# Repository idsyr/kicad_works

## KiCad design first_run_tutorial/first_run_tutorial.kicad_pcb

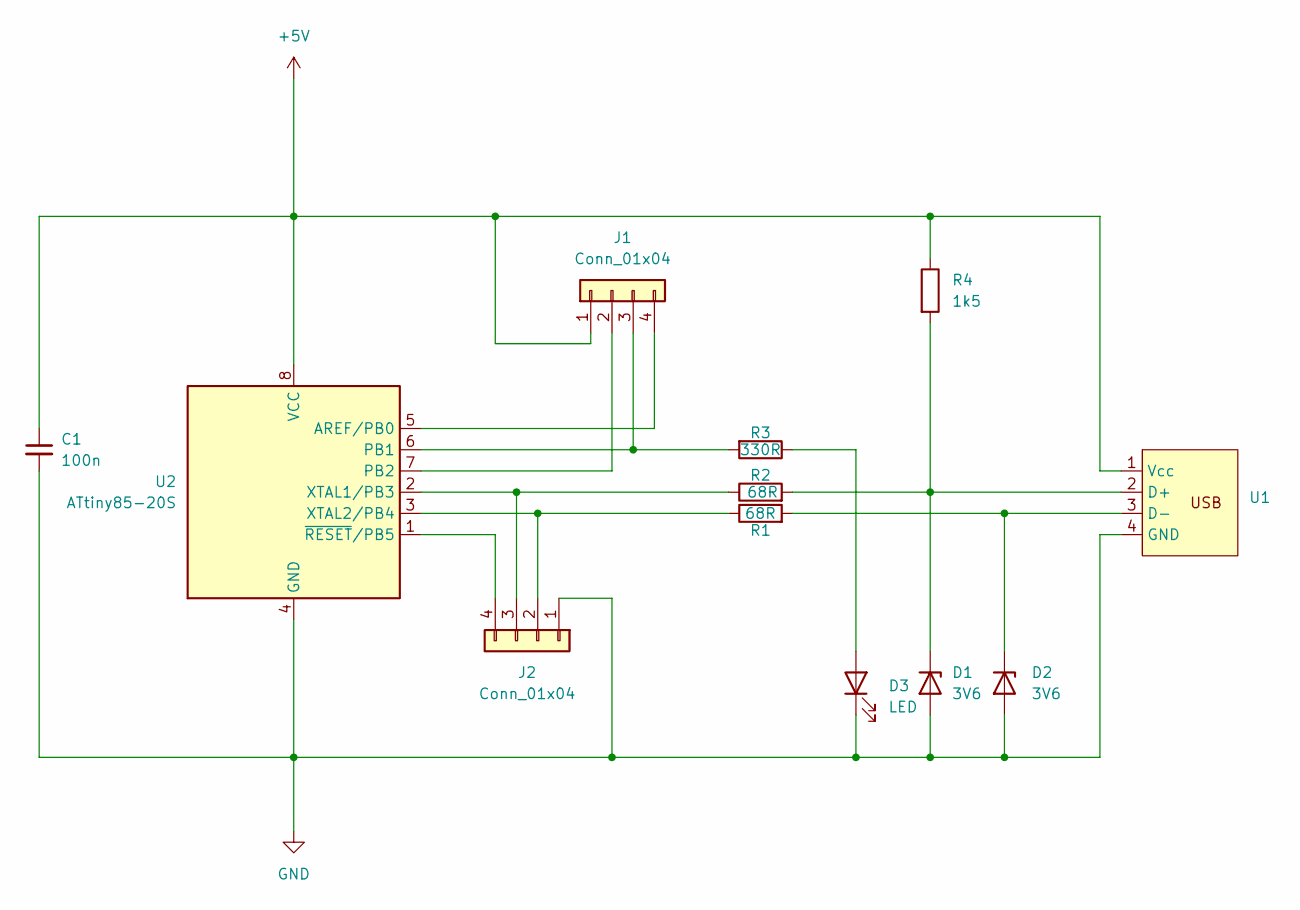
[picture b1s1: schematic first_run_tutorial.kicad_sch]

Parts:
C1: 100n; C_1206_3216Metric_Pad1.33x1.80mm_HandSolder
D1, D2: 3V6; D_SOD-123
D3: LED; LED_D3.0mm
J1, J2: Conn_01x04; PinHeader_1x04_P2.54mm_Vertical
R1, R2: 68R; R_0805_2012Metric_Pad1.20x1.40mm_HandSolder
R3: 330R; R_0805_2012Metric_Pad1.20x1.40mm_HandSolder
R4: 1k5; R_0805_2012Metric_Pad1.20x1.40mm_HandSolder
U1: PSB_USB_connector
U2: ATtiny85-20S; SOIC-8_5.3x5.3mm_P1.27mm

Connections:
+5V: C1.1, J1.1, R4.1, U1.1 (Vcc), U2.8 (VCC); also elsewhere on the board
GND: C1.2, D1.2 (A), D2.2 (A), D3.1 (K), J2.1, U1.4 (GND), U2.4 (GND); also elsewhere on the board
unnamed 2: D1.1 (K), R2.2, R4.2, U1.2 (D+); also elsewhere on the board
unnamed 3: D2.1 (K), R1.2, U1.3 (D-); also elsewhere on the board
unnamed: D3.2 (A), R3.1
unnamed: J1.2, U2.7 (PB2)
unnamed: J1.3, R3.2, U2.6 (PB1)
unnamed: J1.4, U2.5 (AREF/PB0)
unnamed: J2.2, R1.1, U2.3 (XTAL2/PB4)
unnamed: J2.3, R2.1, U2.2 (XTAL1/PB3)
unnamed: J2.4, U2.1 (~RESET/PB5)

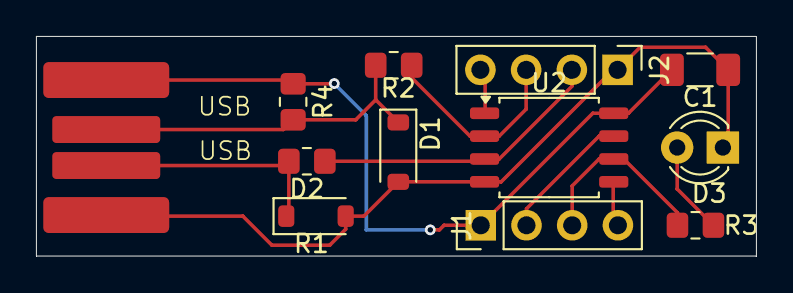
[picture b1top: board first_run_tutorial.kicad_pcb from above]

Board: 2 copper layers, 40.0 x 12.2 mm, 12 parts (0 on the bottom side), 11 nets.

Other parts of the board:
USB: PSB_USB_connector

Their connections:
+5V: USB.1 (Vcc); also elsewhere on the board
GND: USB.4 (GND); also elsewhere on the board
unnamed 2: USB.2 (D+); also elsewhere on the board
unnamed 3: USB.3 (D-); also elsewhere on the board

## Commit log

2025-03-09 init commit
2025-03-09 added: first_run_tutorial
